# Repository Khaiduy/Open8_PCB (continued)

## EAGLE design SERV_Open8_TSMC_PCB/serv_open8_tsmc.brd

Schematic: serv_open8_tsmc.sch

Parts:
C1, C3, C5, C6: 1.0uF; 0603
C2, C4, C7, C8: 4.7uF; 0603
C9, C10: 36pF; 0603
C11, C12: 22pF; 0603
C14, C16, C19, C21: 0.1uF; 0603
C15, C17, C20, C22: 10uF; 0603
CLOCK: PINHD-2X3; 2X03
D1, D2, D3, D4, D5, D6, D7, D8, D9, D10, D11, D12, D16, D17, D18, D19, D20, D21, D22, D27, D28: LED0; LED-0603
FLASH_OPEN8: PINHD-2X6; 2X06
FLASH_SERV: PINHD-2X6; 2X06
GND: PINHD-2X3; 2X03
H1, H2, H3, H4: MOUNT-HOLE3.3; 3,3
IC1, IC2: SN74LVC1GU04DBVR; SOT95P280X145-5N
IN_12_OPEN8: REG_IN_OPEN8; JP1
IN_12_SERV: REG_IN_SERV; JP1
IN_12_VDD: REG_IN; JP1
IN_IO_3V3: REG_IN_IO; JP1
J4: 2985-6004; 29856004
JTAG_OPEN8: PINHD-2X10; 2X10
JTAG_SERV: PINHD-2X10; 2X10
LEDS_OPEN8: PINHD-2X8; 2X08
LEDS_SERV: PINHD-2X8; 2X08
LORA_OPEN8: RFM95W-915S2; RFM95-915S2
LORA_SERV: RFM95W-915S2; RFM95-915S2
NRESET: REG_IN; JP1
NRESET_SERV: REG_IN; JP1
POWER: PINHD-2X4; 2X04
Q1, Q2, Q3, Q4, Q5, Q6, Q7, Q8, Q9, Q10, Q11, Q14, Q15, Q16, Q17, Q18, Q19, Q25, Q26, Q27, Q28: BSH103,235; SOT95P230X110-3N
R1, R7, R13, R16: 66.5KOHM-0603-1/10W-5%; 0603
R2, R8, R14, R17: 1; 0603
R3, R15, R19: 53.6k; 0603
R4, R20: 10M; 0603
R5, R6, R21, R28: 47k; 0603
R9: 3k; 0603
R10: 243k; 0603
R11, R12, R22, R23, R24, R25, R26, R27, R38, R39, R48, R49, R50, R51, R52, R53, R54, R55, R56, R57, R58, R59, R60, R61, R63, R65, R66, R67, R68, R69, R70, R71, R78, R80, R81, R82, R89, R90, R91: 10k; 0603
R18: 2k; 0603
R29: 300k; 0603
R30, R31, R32, R33, R34, R35, R36, R37, R40, R41, R42, R43, R44, R45, R46, R47, R62, R64, R77, R79, R88: 330; 0603
S1, S2, S3, S4, S5, S6, S7, S8, S9, S10, S11, S12, S13, S14, S15, S16, S19, S20: SS12SDP2
SPI_OPEN8_1: SPI1; FE10
SPI_OPEN8_2: SPI0; FE10
SPI_SERV_1: SPI1; FE10
SPI_SERV_2: SPI0; FE10
SWITCH_OPEN8: PINHD-2X8; 2X08
SWITCH_SERV: PINHD-2X8; 2X08
U1, U2, U3, U4: TPS76201DBVR; SOT95P280X145-5N
U$1, U$2, U$3, U$4: 2X41_HEADER
USB-UART_OPEN8_1, USB-UART_OPEN8_2: PINHD-1X4; 1X04
USB-UART_SERV_1, USB-UART_SERV_2: PINHD-1X4; 1X04
Y2: HC-49SM8MHZ20PF30PPM; HC49SM8MHZ20PF30PPM
Y3: Q13FC1350000400

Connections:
1: U$1.1
2: U$1.4
3: U$1.3
8MHZ_CLOCK: CLOCK.3, IC1.4 (Y), R4.2, R18.2
32KHZ_CLOCK: CLOCK.1, IC2.4 (Y), R20.2, R29.2
37: U$1.37
38: U$1.40
39: U$1.39
40: U$1.42
41: U$2.1
42: U$2.4
43: U$2.3
44: U$2.6
45: U$2.5
46: U$2.8
47: U$2.7
48: U$2.10
49: U$2.9
50: U$2.12
51: U$2.11
52: U$2.14
68: U$2.30
69: U$2.29
70: U$2.32
71: U$2.31
72: U$2.34
73: U$2.33
74: U$2.36
75: U$2.35
76: U$2.38
77: U$2.37
78: U$2.40
79: U$2.39
80: U$2.42
81: U$3.1
82: U$3.4
83: U$3.3
117: U$3.37
118: U$3.40
119: U$3.39
120: U$3.42
121: U$4.1
122: U$4.4
123: U$4.3
124: U$4.6
125: U$4.5
126: U$4.8
127: U$4.7
128: U$4.10
129: U$4.9
130: U$4.12
131: U$4.11
132: U$4.14
148: U$4.30
149: U$4.29
150: U$4.32
151: U$4.31
152: U$4.34
153: U$4.33
154: U$4.36
155: U$4.35
156: U$4.38
157: U$4.37
158: U$4.40
159: U$4.39
160: U$4.42
CLOCK: CLOCK.2, CLOCK.4, CLOCK.6, U$1.33, U$3.35
CLOCK_SERV_XO: U$1.36
CLOCK_XO: U$3.36
DIPSW_0: SWITCH_OPEN8.1, U$3.25
DIPSW_1: SWITCH_OPEN8.3, U$3.26
DIPSW_2: SWITCH_OPEN8.5, U$3.23
DIPSW_3: SWITCH_OPEN8.7, U$3.24
DIPSW_4: SWITCH_OPEN8.9, U$3.21
DIPSW_5: SWITCH_OPEN8.11, U$3.16
DIPSW_6: SWITCH_OPEN8.13, U$3.13
DIPSW_7: SWITCH_OPEN8.15, U$3.14
DIPSW_SERV_0: SWITCH_SERV.1, U$1.21
DIPSW_SERV_1: SWITCH_SERV.3, U$1.22
DIPSW_SERV_2: SWITCH_SERV.5, U$1.19
DIPSW_SERV_3: SWITCH_SERV.7, U$1.20
DIPSW_SERV_4: SWITCH_SERV.9, U$1.17
DIPSW_SERV_5: SWITCH_SERV.11, U$1.18
DIPSW_SERV_6: SWITCH_SERV.13, U$1.15
DIPSW_SERV_7: SWITCH_SERV.15, U$1.16
GND: C1.2, C3.2, C5.2, C6.2, C9.2, C10.1, C11.2, C12.1, C14.2, C15.2, C16.2, C17.2, C19.2, C20.2, C21.2, C22.2, FLASH_OPEN8.3, FLASH_OPEN8.4, FLASH_SERV.3, FLASH_SERV.4, GND.1, GND.2, GND.3, GND.4, GND.5, GND.6, J4.1, J4.2, J4.3, J4.4, JTAG_OPEN8.4, JTAG_OPEN8.6, JTAG_OPEN8.8, JTAG_OPEN8.10, JTAG_OPEN8.12, JTAG_OPEN8.14, JTAG_OPEN8.16, JTAG_OPEN8.18, JTAG_OPEN8.20, JTAG_SERV.4, JTAG_SERV.6, JTAG_SERV.8, JTAG_SERV.10, JTAG_SERV.12, JTAG_SERV.14, JTAG_SERV.16, JTAG_SERV.18, JTAG_SERV.20, LORA_OPEN8.P$1 (GND_1), LORA_OPEN8.P$8 (GND_2), LORA_OPEN8.P$15 (GND_3), LORA_SERV.P$1 (GND_1), LORA_SERV.P$8 (GND_2), LORA_SERV.P$15 (GND_3), Q1.2 (S), Q2.2 (S), Q3.2 (S), Q4.2 (S), Q5.2 (S), Q6.2 (S), Q7.2 (S), Q8.2 (S), Q9.2 (S), Q10.2 (S), Q11.2 (S), Q14.2 (S), Q15.2 (S), Q16.2 (S), Q17.2 (S), Q18.2 (S), Q19.2 (S), Q25.2 (S), Q26.2 (S), Q27.2 (S), Q28.2 (S), R1.1, R2.1, R6.1, R7.1, R8.1, R13.1, R14.1, R16.1, R17.1, R28.1, R38.1, R39.1, R48.1, R49.1, R50.1, R51.1, R52.1, R53.1, R54.1, R55.1, R56.1, R57.1, R58.1, R59.1, R60.1, R61.1, R63.1, R65.1, R78.1, R80.1, R91.1, S1.3 (ON_2), S2.3 (ON_2), S3.3 (ON_2), S4.3 (ON_2), S5.3 (ON_2), S6.3 (ON_2), S7.3 (ON_2), S8.3 (ON_2), S9.3 (ON_2), S10.3 (ON_2), S11.3 (ON_2), S12.3 (ON_2), S13.3 (ON_2), S14.3 (ON_2), S15.3 (ON_2), S16.3 (ON_2), S19.3 (ON_2), S20.3 (ON_2), SPI_OPEN8_2.10, SPI_SERV_2.10, U1.2 (GND), U1.3 (!EN), U2.2 (GND), U2.3 (!EN), U3.2 (GND), U3.3 (!EN), U4.2 (GND), U4.3 (!EN), U$1.24, U$2.20, U$2.22, U$3.19, U$3.22, U$4.21, U$4.22, U$4.24, USB-UART_OPEN8_1.1, USB-UART_SERV_1.1
IN_12_OPEN8: C6.1, IN_12_OPEN8.2, U4.1 (IN)
IN_12_SERV: C1.1, IN_12_SERV.2, U1.1 (IN)
IN_12_VDD: C5.1, IN_12_VDD.2, U3.1 (IN)
IN_IO: C3.1, IN_IO_3V3.2, U2.1 (IN)
I_PROG_COPI: SPI_OPEN8_2.3, U$3.12
I_PROG_CS: SPI_OPEN8_2.4, U$3.10
I_PROG_SCK: SPI_OPEN8_2.1, U$3.11
I_SPIFLASH_CIPO: FLASH_OPEN8.8, U$2.15
I_SPI_CIPO: LORA_OPEN8.P$3 (MOSI), U$2.26
I_TCK: JTAG_OPEN8.9, U$3.7
I_TDI: JTAG_OPEN8.5, U$3.8
I_TMS: JTAG_OPEN8.7, U$3.6
I_TRST: JTAG_OPEN8.3, U$2.27
LEDS_0: LEDS_OPEN8.1, U$3.33
LEDS_1: LEDS_OPEN8.3, U$3.34
LEDS_2: LEDS_OPEN8.5, U$3.31
LEDS_3: LEDS_OPEN8.7, U$3.32
LEDS_4: LEDS_OPEN8.9, U$3.29
LEDS_5: LEDS_OPEN8.11, U$3.30
LEDS_6: LEDS_OPEN8.13, U$3.27
LEDS_7: LEDS_OPEN8.15, U$3.28
LEDS_SERV_0: LEDS_SERV.1, U$1.34
LEDS_SERV_1: LEDS_SERV.3, U$1.31
LEDS_SERV_2: LEDS_SERV.5, U$1.32
LEDS_SERV_3: LEDS_SERV.7, U$1.29
LEDS_SERV_4: LEDS_SERV.9, U$1.30
LEDS_SERV_5: LEDS_SERV.11, U$1.27
LEDS_SERV_6: LEDS_SERV.13, U$1.28
LEDS_SERV_7: LEDS_SERV.15, U$1.25
unnamed: R1.2, R3.1, U1.4 (FB)
unnamed: C2.2, R2.2
unnamed: NRESET.2, S19.2 (COM)
unnamed: IC1.3 (GND), R6.2
unnamed: C9.1, IC1.2 (A), R4.1, Y2.2 (CRYSTAL_2)
unnamed: R7.2, R10.1, U2.4 (FB)
unnamed: C4.2, R8.2
unnamed: R9.1, R10.2
unnamed: C10.2, R18.1, Y2.1 (CRYSTAL_1)
unnamed: R11.1, S1.1 (ON_1)
unnamed: R12.1, S2.1 (ON_1)
unnamed: R13.2, R19.1, U3.4 (FB)
unnamed: C8.2, R14.2
unnamed: IC1.5 (VCC), R5.1
unnamed: D12.A, R88.1
unnamed: R22.1, S3.1 (ON_1)
unnamed: R23.1, S4.1 (ON_1)
unnamed: R24.1, S5.1 (ON_1)
unnamed: R25.1, S6.1 (ON_1)
unnamed: R26.1, S7.1 (ON_1)
unnamed: R27.1, S8.1 (ON_1)
unnamed: S5.2 (COM), SWITCH_SERV.10
unnamed: S6.2 (COM), SWITCH_SERV.12
unnamed: S7.2 (COM), SWITCH_SERV.14
unnamed: S8.2 (COM), SWITCH_SERV.16
unnamed: S4.2 (COM), SWITCH_SERV.8
unnamed: S3.2 (COM), SWITCH_SERV.6
unnamed: S2.2 (COM), SWITCH_SERV.4
unnamed: S1.2 (COM), SWITCH_SERV.2
unnamed: R15.1, R16.2, U4.4 (FB)
unnamed: IC2.3 (GND), R28.2
unnamed: C7.2, R17.2
unnamed: C11.1, IC2.2 (A), R20.1, Y3.2 (CRYSTAL_2)
unnamed: C12.2, R29.1, Y3.1 (CRYSTAL_1)
unnamed: NRESET_SERV.2, S20.2 (COM)
unnamed: IC2.5 (VCC), R21.1
unnamed: D1.A, R30.1
unnamed: D1.C, Q1.3 (D)
unnamed: D2.A, R31.1
unnamed: D2.C, Q2.3 (D)
unnamed: R81.1, S19.1 (ON_1)
unnamed: R82.1, S20.1 (ON_1)
unnamed: D12.C, Q11.3 (D)
unnamed: D3.A, R32.1
unnamed: D3.C, Q14.3 (D)
unnamed: D4.A, R40.1
unnamed: D4.C, Q3.3 (D)
unnamed: D5.A, R41.1
unnamed: D16.A, R33.1
unnamed: D16.C, Q15.3 (D)
unnamed: D17.A, R34.1
unnamed: D17.C, Q25.3 (D)
unnamed: D18.A, R35.1
unnamed: D18.C, Q26.3 (D)
unnamed: D27.A, R36.1
unnamed: D27.C, Q27.3 (D)
unnamed: D28.A, R37.1
unnamed: D28.C, Q28.3 (D)
unnamed: D19.A, R62.1
unnamed: D5.C, Q4.3 (D)
unnamed: D6.A, R42.1
unnamed: D6.C, Q5.3 (D)
unnamed: D7.A, R43.1
unnamed: D7.C, Q6.3 (D)
unnamed: D8.A, R44.1
unnamed: D8.C, Q7.3 (D)
unnamed: D9.A, R45.1
unnamed: D19.C, Q16.3 (D)
unnamed: D20.A, R64.1
unnamed: D20.C, Q17.3 (D)
unnamed: D21.A, R77.1
unnamed: D21.C, Q18.3 (D)
unnamed: D22.A, R79.1
unnamed: D22.C, Q19.3 (D)
unnamed: D9.C, Q8.3 (D)
unnamed: D10.A, R46.1
unnamed: D10.C, Q9.3 (D)
unnamed: D11.A, R47.1
unnamed: D11.C, Q10.3 (D)
unnamed: R66.1, S9.1 (ON_1)
unnamed: R67.1, S10.1 (ON_1)
unnamed: R68.1, S11.1 (ON_1)
unnamed: R69.1, S12.1 (ON_1)
unnamed: R70.1, S13.1 (ON_1)
unnamed: R71.1, S14.1 (ON_1)
unnamed: R89.1, S15.1 (ON_1)
unnamed: R90.1, S16.1 (ON_1)
unnamed: S13.2 (COM), SWITCH_OPEN8.10
unnamed: S14.2 (COM), SWITCH_OPEN8.12
unnamed: S15.2 (COM), SWITCH_OPEN8.14
unnamed: S16.2 (COM), SWITCH_OPEN8.16
unnamed: S12.2 (COM), SWITCH_OPEN8.8
unnamed: S11.2 (COM), SWITCH_OPEN8.6
unnamed: S10.2 (COM), SWITCH_OPEN8.4
unnamed: S9.2 (COM), SWITCH_OPEN8.2
NRESET: NRESET.1, U$3.38
NRESET_SERV: NRESET_SERV.1, U$1.35
OPEN8_OUT_0: LEDS_OPEN8.2, Q3.1 (G), R48.2
OPEN8_OUT_1: LEDS_OPEN8.4, Q4.1 (G), R49.2
OPEN8_OUT_2: LEDS_OPEN8.6, Q5.1 (G), R50.2
OPEN8_OUT_3: LEDS_OPEN8.8, Q6.1 (G), R51.2
OPEN8_OUT_4: LEDS_OPEN8.10, Q7.1 (G), R52.2
OPEN8_OUT_5: LEDS_OPEN8.12, Q8.1 (G), R53.2
OPEN8_OUT_6: LEDS_OPEN8.14, Q9.1 (G), R54.2
OPEN8_OUT_7: LEDS_OPEN8.16, Q10.1 (G), R55.2
OUT_12_OPEN8: C7.1, POWER.1, R15.2, U4.5 (OUT)
OUT_12_SERV: C2.1, POWER.3, R3.2, U1.5 (OUT)
OUT_12_VDD: C8.1, POWER.5, R19.2, U3.5 (OUT)
OUT_IO_3V3: C4.1, POWER.7, R9.2, U2.5 (OUT)
O_PROG_CIPO: SPI_OPEN8_2.2, U$3.9
O_SPIFLASH_COPI: FLASH_OPEN8.10, U$2.18
O_SPIFLASH_CS: FLASH_OPEN8.12, U$2.16
O_SPIFLASH_SCK: FLASH_OPEN8.6, U$2.17
O_SPI_COPI: LORA_OPEN8.P$2 (MISO), U$2.25
O_SPI_CS: LORA_OPEN8.P$5 (NSS), U$2.23
O_SPI_SCK: LORA_OPEN8.P$4 (SCK), U$2.28
O_TDO: JTAG_OPEN8.13, U$3.5
RX_IN: U$1.38, USB-UART_OPEN8_1.2
SERV_I_PROG_COPI: SPI_SERV_2.3, U$1.14
SERV_I_PROG_CS: SPI_SERV_2.4, U$1.12
SERV_I_PROG_SCK: SPI_SERV_2.1, U$1.13
SERV_I_SPIFLASH_CIPO: FLASH_SERV.8, U$4.26
SERV_I_SPI_CIPO: LORA_SERV.P$3 (MOSI), U$4.16
SERV_I_TCK: JTAG_SERV.9, U$1.9
SERV_I_TDI: JTAG_SERV.5, U$1.10
SERV_I_TMS: JTAG_SERV.7, U$1.8
SERV_I_TRST: JTAG_SERV.3, U$1.5
SERV_OUT_0: LEDS_SERV.2, Q1.1 (G), R38.2
SERV_OUT_1: LEDS_SERV.4, Q2.1 (G), R39.2
SERV_OUT_2: LEDS_SERV.6, Q14.1 (G), R56.2
SERV_OUT_3: LEDS_SERV.8, Q15.1 (G), R57.2
SERV_OUT_4: LEDS_SERV.10, Q25.1 (G), R58.2
SERV_OUT_5: LEDS_SERV.12, Q26.1 (G), R59.2
SERV_OUT_6: LEDS_SERV.14, Q27.1 (G), R60.2
SERV_OUT_7: LEDS_SERV.16, Q28.1 (G), R61.2
SERV_O_PROG_CIPO: SPI_SERV_2.2, U$1.11
SERV_O_SPIFLASH_COPI: FLASH_SERV.10, U$4.17
SERV_O_SPIFLASH_CS: FLASH_SERV.12, U$4.25
SERV_O_SPIFLASH_SCK: FLASH_SERV.6, U$4.18
SERV_O_SPI_COPI: LORA_SERV.P$2 (MISO), U$4.13
SERV_O_SPI_CS: LORA_SERV.P$5 (NSS), U$4.15
SERV_O_SPI_SCK: LORA_SERV.P$4 (SCK), U$1.6
SERV_O_TDO: JTAG_SERV.13, U$1.7
SERV_RX_IN: U$4.27, USB-UART_SERV_1.2
SERV_TX_OUT: U$4.28, USB-UART_SERV_1.4
SMA_CLK: CLOCK.5, J4.5
TX_OUT: U$2.13, USB-UART_OPEN8_1.4
VDD_3V3: C21.1, C22.1, FLASH_OPEN8.1, FLASH_OPEN8.2, FLASH_SERV.1, FLASH_SERV.2, JTAG_OPEN8.1, JTAG_OPEN8.2, JTAG_SERV.1, JTAG_SERV.2, LORA_OPEN8.P$12 (3.3V), LORA_SERV.P$12 (3.3V), POWER.8, Q16.1 (G), R5.2, R11.2, R12.2, R21.2, R22.2, R23.2, R24.2, R25.2, R26.2, R27.2, R30.2, R31.2, R32.2, R33.2, R34.2, R35.2, R36.2, R37.2, R40.2, R41.2, R42.2, R43.2, R44.2, R45.2, R46.2, R47.2, R62.2, R63.2, R64.2, R66.2, R67.2, R68.2, R69.2, R70.2, R71.2, R77.2, R79.2, R81.2, R82.2, R88.2, R89.2, R90.2, U$1.26, U$2.24, U$3.15, U$3.18, U$4.20, USB-UART_OPEN8_1.3, USB-UART_SERV_1.3
VDD_5V: IN_12_OPEN8.1, IN_12_SERV.1, IN_12_VDD.1, IN_IO_3V3.1, Q11.1 (G), R91.2, USB-UART_OPEN8_2.2, USB-UART_SERV_2.2
VO_12_OPEN8: C14.1, C15.1, POWER.2, Q17.1 (G), R65.2, U$4.23
VO_12_SERV: C16.1, C17.1, POWER.4, Q18.1 (G), R78.2, U$2.19
VO_12_VDD: C19.1, C20.1, POWER.6, Q19.1 (G), R80.2, U$1.23, U$2.21, U$3.17, U$3.20, U$4.19

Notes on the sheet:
Regulator - 5V to 1.2V
CHIP SOCKET
POWER
CLOCK GENERATOR
RESET
Mounting holes
UART_OPEN8
FLASH_OPEN8
LORA_OPEN8
JTAG_OPEN8
FLASH_SERV
UART_SERV
SPI_SERV
JTAG_SERV
SPI_OPEN8
SWITCH_OPEN8
32KHZ
8MHZ
SMA
LEDS_OPEn8
SWITCH_SERV
LEDS_SERV
LORA_SERV

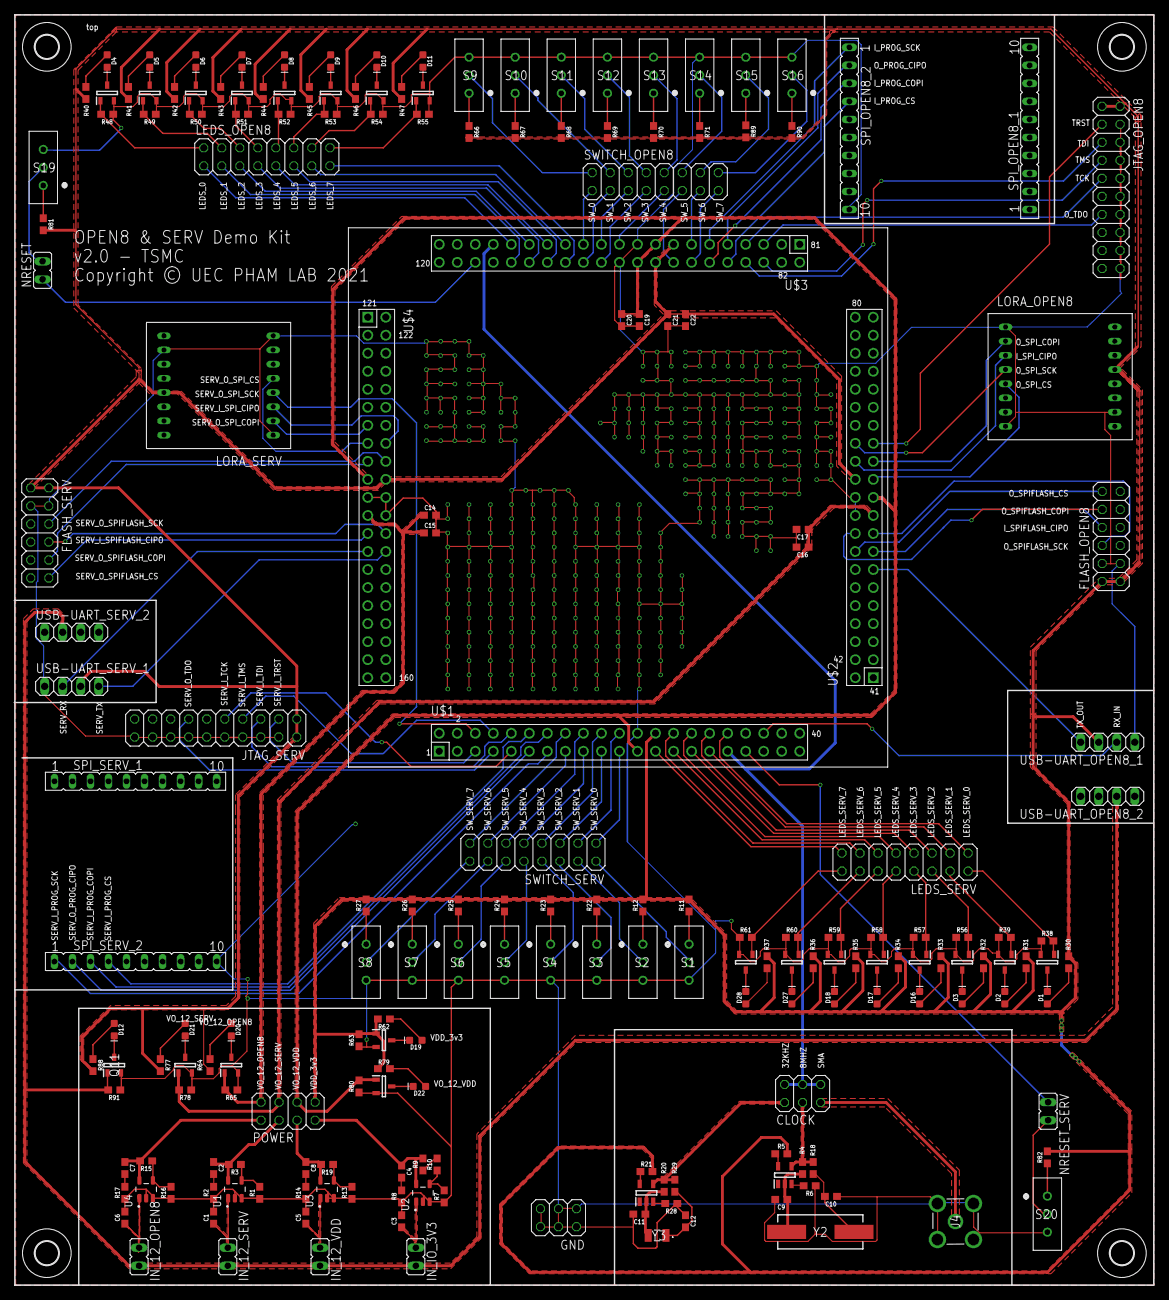
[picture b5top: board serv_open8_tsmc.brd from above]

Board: 2 copper layers, 160.5 x 179.0 mm, 205 parts (0 on the bottom side), 201 nets.

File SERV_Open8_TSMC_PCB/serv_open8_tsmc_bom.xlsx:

Comment | Designator | Footprint | LCSC Part #（optional）
0.1uF | C14, C16, C19, C21 | 603 | C77055
1 OHM | R2, R8, R14, R17 | 603 | C247057
1.0uF | C1, C3, C5, C6 | 603 | C1689
10M OHM | R4, R20 | 603 | C7250
10kOHM | R11, R12, R22, R23, R24, R25, R26, R27, R38, R39, R48, R49, R50, R51, R52, R53,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 | 603 | C25804
10uF | C15, C17, C20, C22 | 603 | C85713
22pF | C11, C12 | 603 | C1653
243kOHM | R10 | 603 | C23351
2kOHM | R18 | 603 | C22900
300kOHM | R29 | 603 | C23024
330OHM | R30, R31, R32, R33, R34, R35, R36, R37, R40, R41, R42, R43, R44, R45, R46, R47,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 | 603 | C23138
36pF | C9, C10 | 603 | C159790
3kOHM | R9 | 603 | C4211
4.7uF | C2, C4, C7, C8 | 603 | C19666
47kOHM | R5, R6, R21, R28 | 603 | C25819
53.6kOHM | R3, R15, R19 | 603 | C23074
66.5KOHM | R1, R7, R13, R16 | 603 | C23225
BSH103,235 | Q1, Q2, Q3, Q4, Q5, Q6, Q7, Q8, Q9, Q10, Q11, Q14, Q15, Q16, Q17, Q18, Q19, Q25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 | SOT-23-3 | C88711
HC-49SM8MHZ20PF30PPM | Y2 | SMD-CRY-3.8x13.5_2P | C107426
LED | D1, D2, D3, D4, D5, D6, D7, D8, D9, D10, D11, D12, D16, D17, D18, D19, D20, D21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 | 603 | C2286
Q13FC1350000400 | Y3 | SMD-3215_2P | C32346
SN74LVC1GU04DBVR | IC1, IC2 | SOT-23-5 | C81934
TPS76201DBVR | U1, U2, U3, U4 | SOT-23-5 | C13997

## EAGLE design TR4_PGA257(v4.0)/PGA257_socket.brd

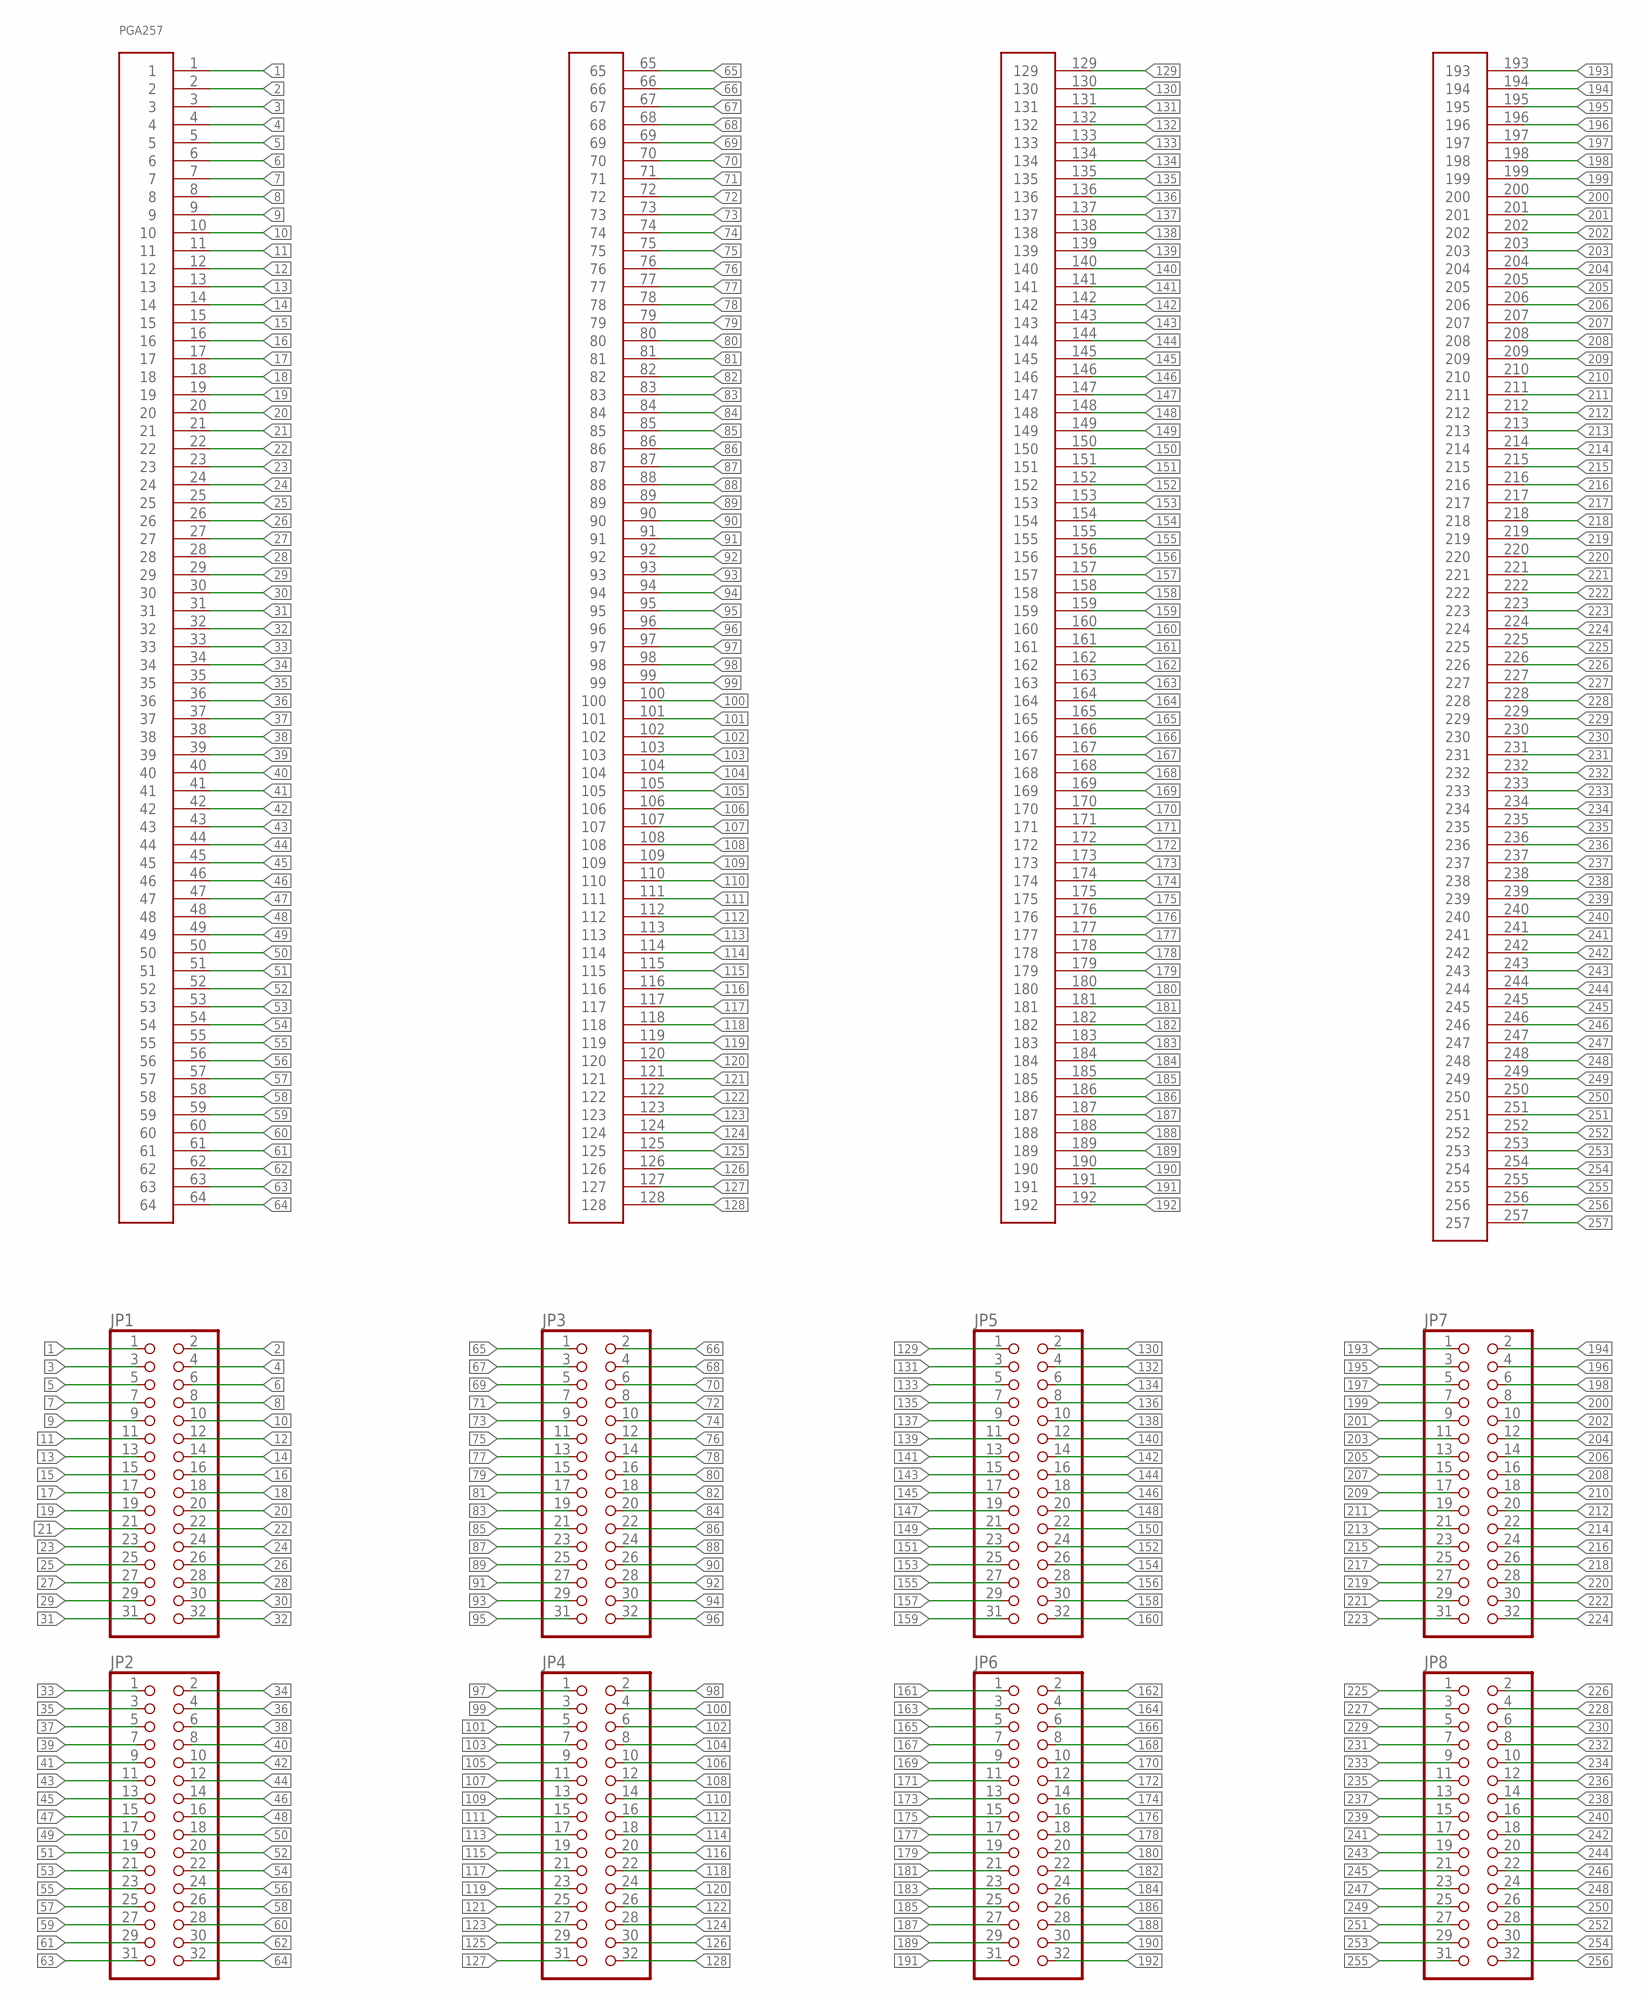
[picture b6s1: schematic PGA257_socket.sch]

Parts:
JP1, JP2, JP3, JP4, JP5, JP6, JP7, JP8: PINHD-2X16; 2X16
PGA257: PGA257

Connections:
1: JP1.1, PGA257.1
2: JP1.2, PGA257.2
3: JP1.3, PGA257.3
4: JP1.4, PGA257.4
5: JP1.5, PGA257.5
6: JP1.6, PGA257.6
7: JP1.7, PGA257.7
8: JP1.8, PGA257.8
9: JP1.9, PGA257.9
10: JP1.10, PGA257.10
11: JP1.11, PGA257.11
12: JP1.12, PGA257.12
13: JP1.13, PGA257.13
14: JP1.14, PGA257.14
15: JP1.15, PGA257.15
16: JP1.16, PGA257.16
17: JP1.17, PGA257.17
18: JP1.18, PGA257.18
19: JP1.19, PGA257.19
20: JP1.20, PGA257.20
21: JP1.21, PGA257.21
22: JP1.22, PGA257.22
23: JP1.23, PGA257.23
24: JP1.24, PGA257.24
25: JP1.25, PGA257.25
26: JP1.26, PGA257.26
27: JP1.27, PGA257.27
28: JP1.28, PGA257.28
29: JP1.29, PGA257.29
30: JP1.30, PGA257.30
31: JP1.31, PGA257.31
32: JP1.32, PGA257.32
33: JP2.1, PGA257.33
34: JP2.2, PGA257.34
35: JP2.3, PGA257.35
36: JP2.4, PGA257.36
37: JP2.5, PGA257.37
38: JP2.6, PGA257.38
39: JP2.7, PGA257.39
40: JP2.8, PGA257.40
41: JP2.9, PGA257.41
42: JP2.10, PGA257.42
43: JP2.11, PGA257.43
44: JP2.12, PGA257.44
45: JP2.13, PGA257.45
46: JP2.14, PGA257.46
47: JP2.15, PGA257.47
48: JP2.16, PGA257.48
49: JP2.17, PGA257.49
50: JP2.18, PGA257.50
51: JP2.19, PGA257.51
52: JP2.20, PGA257.52
53: JP2.21, PGA257.53
54: JP2.22, PGA257.54
55: JP2.23, PGA257.55
56: JP2.24, PGA257.56
57: JP2.25, PGA257.57
58: JP2.26, PGA257.58
59: JP2.27, PGA257.59
60: JP2.28, PGA257.60
61: JP2.29, PGA257.61
62: JP2.30, PGA257.62
63: JP2.31, PGA257.63
64: JP2.32, PGA257.64
65: JP3.1, PGA257.65
66: JP3.2, PGA257.66
67: JP3.3, PGA257.67
68: JP3.4, PGA257.68
69: JP3.5, PGA257.69
70: JP3.6, PGA257.70
71: JP3.7, PGA257.71
72: JP3.8, PGA257.72
73: JP3.9, PGA257.73
74: JP3.10, PGA257.74
75: JP3.11, PGA257.75
76: JP3.12, PGA257.76
77: JP3.13, PGA257.77
78: JP3.14, PGA257.78
79: JP3.15, PGA257.79
80: JP3.16, PGA257.80
81: JP3.17, PGA257.81
82: JP3.18, PGA257.82
83: JP3.19, PGA257.83
84: JP3.20, PGA257.84
85: JP3.21, PGA257.85
86: JP3.22, PGA257.86
87: JP3.23, PGA257.87
88: JP3.24, PGA257.88
89: JP3.25, PGA257.89
90: JP3.26, PGA257.90
91: JP3.27, PGA257.91
92: JP3.28, PGA257.92
93: JP3.29, PGA257.93
94: JP3.30, PGA257.94
95: JP3.31, PGA257.95
96: JP3.32, PGA257.96
97: JP4.1, PGA257.97
98: JP4.2, PGA257.98
99: JP4.3, PGA257.99
100: JP4.4, PGA257.100
101: JP4.5, PGA257.101
102: JP4.6, PGA257.102
103: JP4.7, PGA257.103
104: JP4.8, PGA257.104
105: JP4.9, PGA257.105
106: JP4.10, PGA257.106
107: JP4.11, PGA257.107
108: JP4.12, PGA257.108
109: JP4.13, PGA257.109
110: JP4.14, PGA257.110
111: JP4.15, PGA257.111
112: JP4.16, PGA257.112
113: JP4.17, PGA257.113
114: JP4.18, PGA257.114
115: JP4.19, PGA257.115
116: JP4.20, PGA257.116
117: JP4.21, PGA257.117
118: JP4.22, PGA257.118
119: JP4.23, PGA257.119
120: JP4.24, PGA257.120
121: JP4.25, PGA257.121
122: JP4.26, PGA257.122
123: JP4.27, PGA257.123
124: JP4.28, PGA257.124
125: JP4.29, PGA257.125
126: JP4.30, PGA257.126
127: JP4.31, PGA257.127
128: JP4.32, PGA257.128
129: JP5.1, PGA257.129
130: JP5.2, PGA257.130
131: JP5.3, PGA257.131
132: JP5.4, PGA257.132
133: JP5.5, PGA257.133
134: JP5.6, PGA257.134
135: JP5.7, PGA257.135
136: JP5.8, PGA257.136
137: JP5.9, PGA257.137
138: JP5.10, PGA257.138
139: JP5.11, PGA257.139
140: JP5.12, PGA257.140
141: JP5.13, PGA257.141
142: JP5.14, PGA257.142
143: JP5.15, PGA257.143
144: JP5.16, PGA257.144
145: JP5.17, PGA257.145
146: JP5.18, PGA257.146
147: JP5.19, PGA257.147
148: JP5.20, PGA257.148
149: JP5.21, PGA257.149
150: JP5.22, PGA257.150
151: JP5.23, PGA257.151
152: JP5.24, PGA257.152
153: JP5.25, PGA257.153
154: JP5.26, PGA257.154
155: JP5.27, PGA257.155
156: JP5.28, PGA257.156
157: JP5.29, PGA257.157
158: JP5.30, PGA257.158
159: JP5.31, PGA257.159
160: JP5.32, PGA257.160
161: JP6.1, PGA257.161
162: JP6.2, PGA257.162
163: JP6.3, PGA257.163
164: JP6.4, PGA257.164
165: JP6.5, PGA257.165
166: JP6.6, PGA257.166
167: JP6.7, PGA257.167
168: JP6.8, PGA257.168
169: JP6.9, PGA257.169
170: JP6.10, PGA257.170
171: JP6.11, PGA257.171
172: JP6.12, PGA257.172
173: JP6.13, PGA257.173
174: JP6.14, PGA257.174
175: JP6.15, PGA257.175
176: JP6.16, PGA257.176
177: JP6.17, PGA257.177
178: JP6.18, PGA257.178
179: JP6.19, PGA257.179
180: JP6.20, PGA257.180
181: JP6.21, PGA257.181
182: JP6.22, PGA257.182
183: JP6.23, PGA257.183
184: JP6.24, PGA257.184
185: JP6.25, PGA257.185
186: JP6.26, PGA257.186
187: JP6.27, PGA257.187
188: JP6.28, PGA257.188
189: JP6.29, PGA257.189
190: JP6.30, PGA257.190
191: JP6.31, PGA257.191
192: JP6.32, PGA257.192
193: JP7.1, PGA257.193
194: JP7.2, PGA257.194
195: JP7.3, PGA257.195
196: JP7.4, PGA257.196
197: JP7.5, PGA257.197
198: JP7.6, PGA257.198
199: JP7.7, PGA257.199
200: JP7.8, PGA257.200
201: JP7.9, PGA257.201
202: JP7.10, PGA257.202
203: JP7.11, PGA257.203
204: JP7.12, PGA257.204
205: JP7.13, PGA257.205
206: JP7.14, PGA257.206
207: JP7.15, PGA257.207
208: JP7.16, PGA257.208
209: JP7.17, PGA257.209
210: JP7.18, PGA257.210
211: JP7.19, PGA257.211
212: JP7.20, PGA257.212
213: JP7.21, PGA257.213
214: JP7.22, PGA257.214
215: JP7.23, PGA257.215
216: JP7.24, PGA257.216
217: JP7.25, PGA257.217
218: JP7.26, PGA257.218
219: JP7.27, PGA257.219
220: JP7.28, PGA257.220
221: JP7.29, PGA257.221
222: JP7.30, PGA257.222
223: JP7.31, PGA257.223
224: JP7.32, PGA257.224
225: JP8.1, PGA257.225
226: JP8.2, PGA257.226
227: JP8.3, PGA257.227
228: JP8.4, PGA257.228
229: JP8.5, PGA257.229
230: JP8.6, PGA257.230
231: JP8.7, PGA257.231
232: JP8.8, PGA257.232
233: JP8.9, PGA257.233
234: JP8.10, PGA257.234
235: JP8.11, PGA257.235
236: JP8.12, PGA257.236
237: JP8.13, PGA257.237
238: JP8.14, PGA257.238
239: JP8.15, PGA257.239
240: JP8.16, PGA257.240
241: JP8.17, PGA257.241
242: JP8.18, PGA257.242
243: JP8.19, PGA257.243
244: JP8.20, PGA257.244
245: JP8.21, PGA257.245
246: JP8.22, PGA257.246
247: JP8.23, PGA257.247
248: JP8.24, PGA257.248
249: JP8.25, PGA257.249
250: JP8.26, PGA257.250
251: JP8.27, PGA257.251
252: JP8.28, PGA257.252
253: JP8.29, PGA257.253
254: JP8.30, PGA257.254
255: JP8.31, PGA257.255
256: JP8.32, PGA257.256
257: PGA257.257

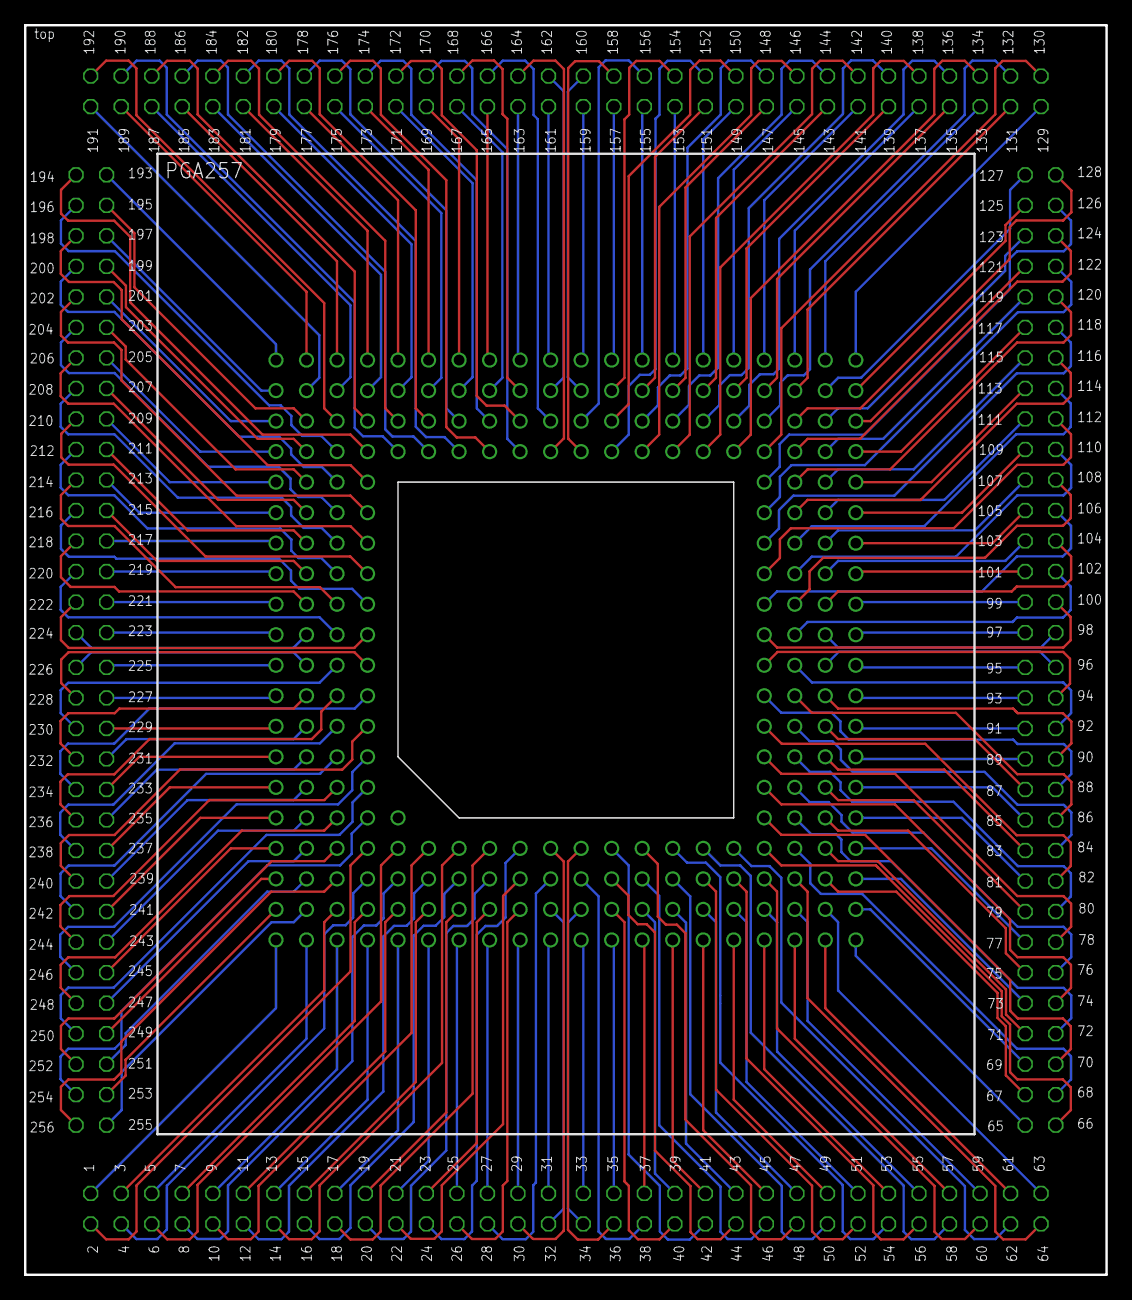
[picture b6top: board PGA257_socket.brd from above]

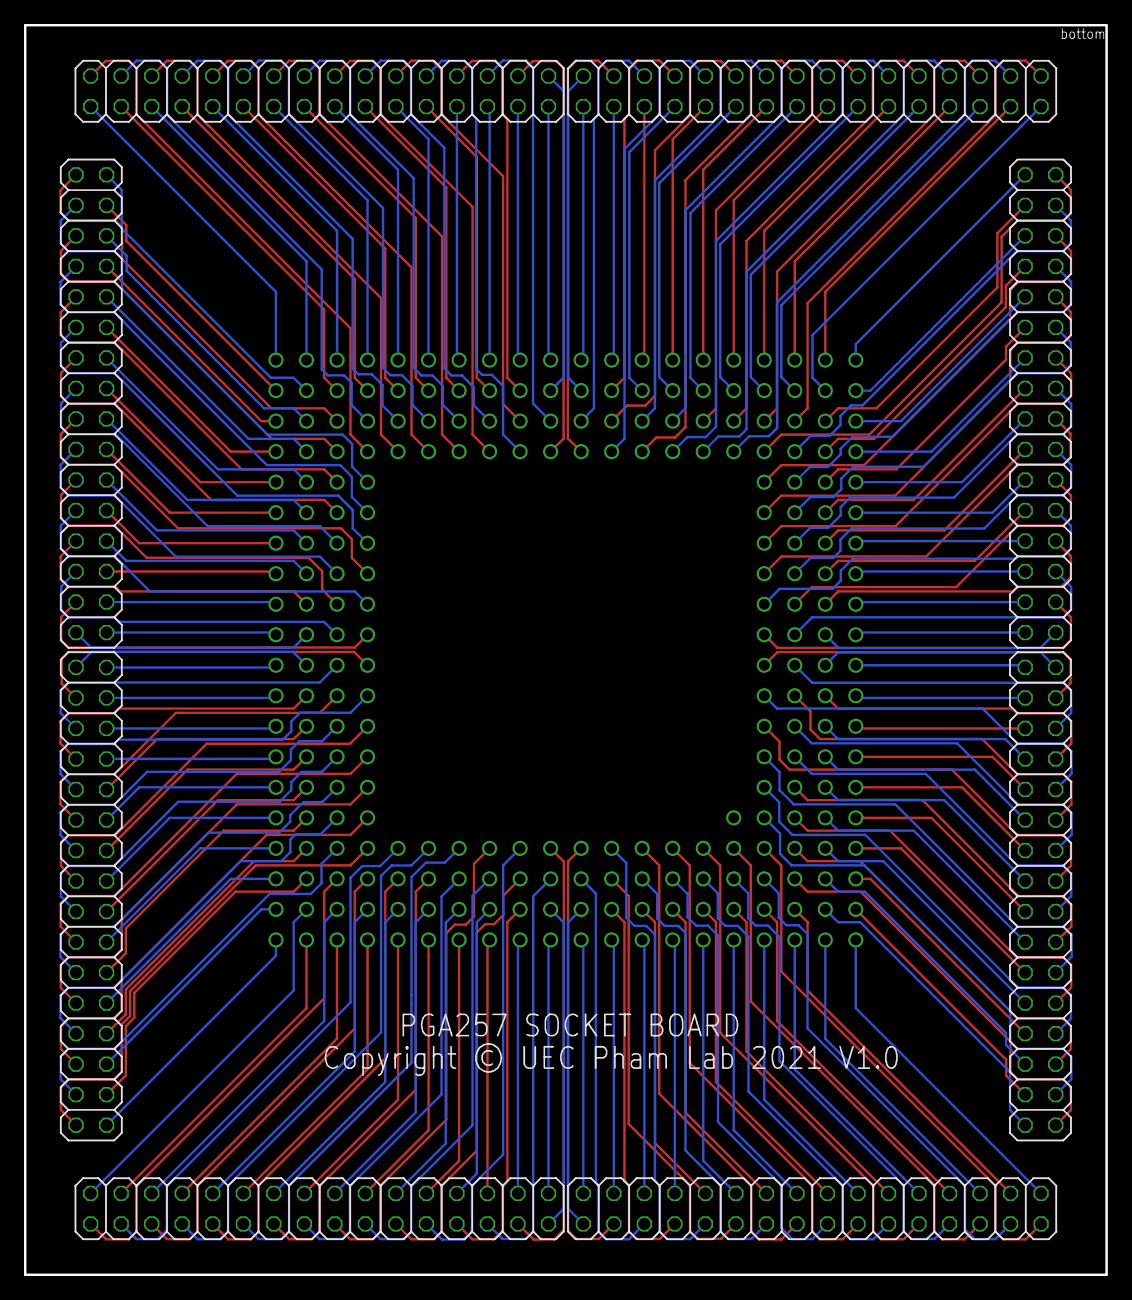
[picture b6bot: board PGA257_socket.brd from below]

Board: 2 copper layers, 90.0 x 104.0 mm, 9 parts (8 on the bottom side), 256 nets.
